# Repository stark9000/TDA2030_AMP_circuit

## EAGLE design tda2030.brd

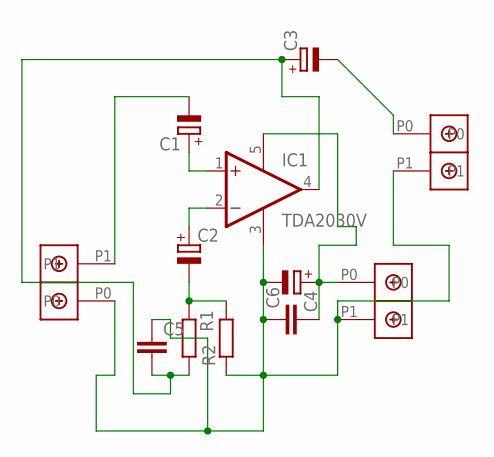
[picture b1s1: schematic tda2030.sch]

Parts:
12V: DBCONN-1X2
AUDIOIN: DBCONN-1X2
C1: CPOL-EUE2.5-6; E2,5-6
C2: CPOL-EUE3.5-8; E3,5-8
C3, C4: CPOL-EUE3.5-10; E3,5-10
C5, C6: C-EU050-025X075; C050-025X075
IC1: TDA2030V; CB360
R1: R-EU_0204/7; 0204/7
R2: R-EU_0204/2V; 0204V
SPEAKER: DBCONN-1X2

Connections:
unnamed: C1.+, IC1.1 (+IN)
unnamed: C2.+, IC1.2 (-IN)
unnamed: C3.+, C5.2, IC1.4 (OUT), R1.2
unnamed: 12V.P1, AUDIOIN.P0, C4.-, C5.1, C6.1, IC1.3 (GND), R2.1, SPEAKER.P1
unnamed: C2.-, R1.1, R2.2
unnamed: 12V.P0, C4.+, C6.2, IC1.5 (V+)
unnamed: AUDIOIN.P1, C1.-
unnamed: C3.-, SPEAKER.P0

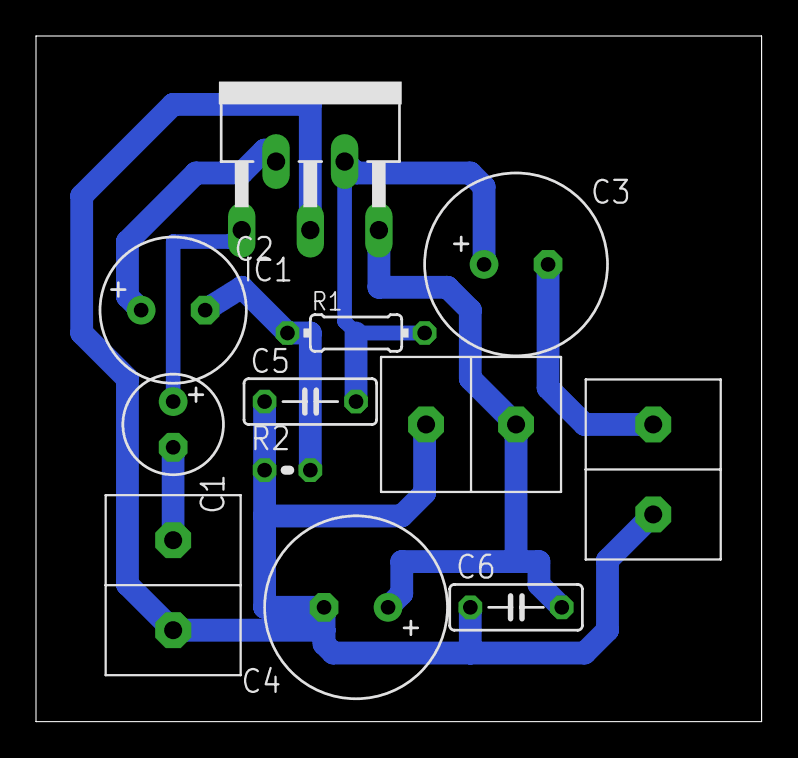
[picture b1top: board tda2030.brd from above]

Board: 2 copper layers, 40.3 x 38.1 mm, 12 parts (0 on the bottom side), 8 nets.
